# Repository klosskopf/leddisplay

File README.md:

# leddisplay
A 10x10 led display with ice40 FPGA

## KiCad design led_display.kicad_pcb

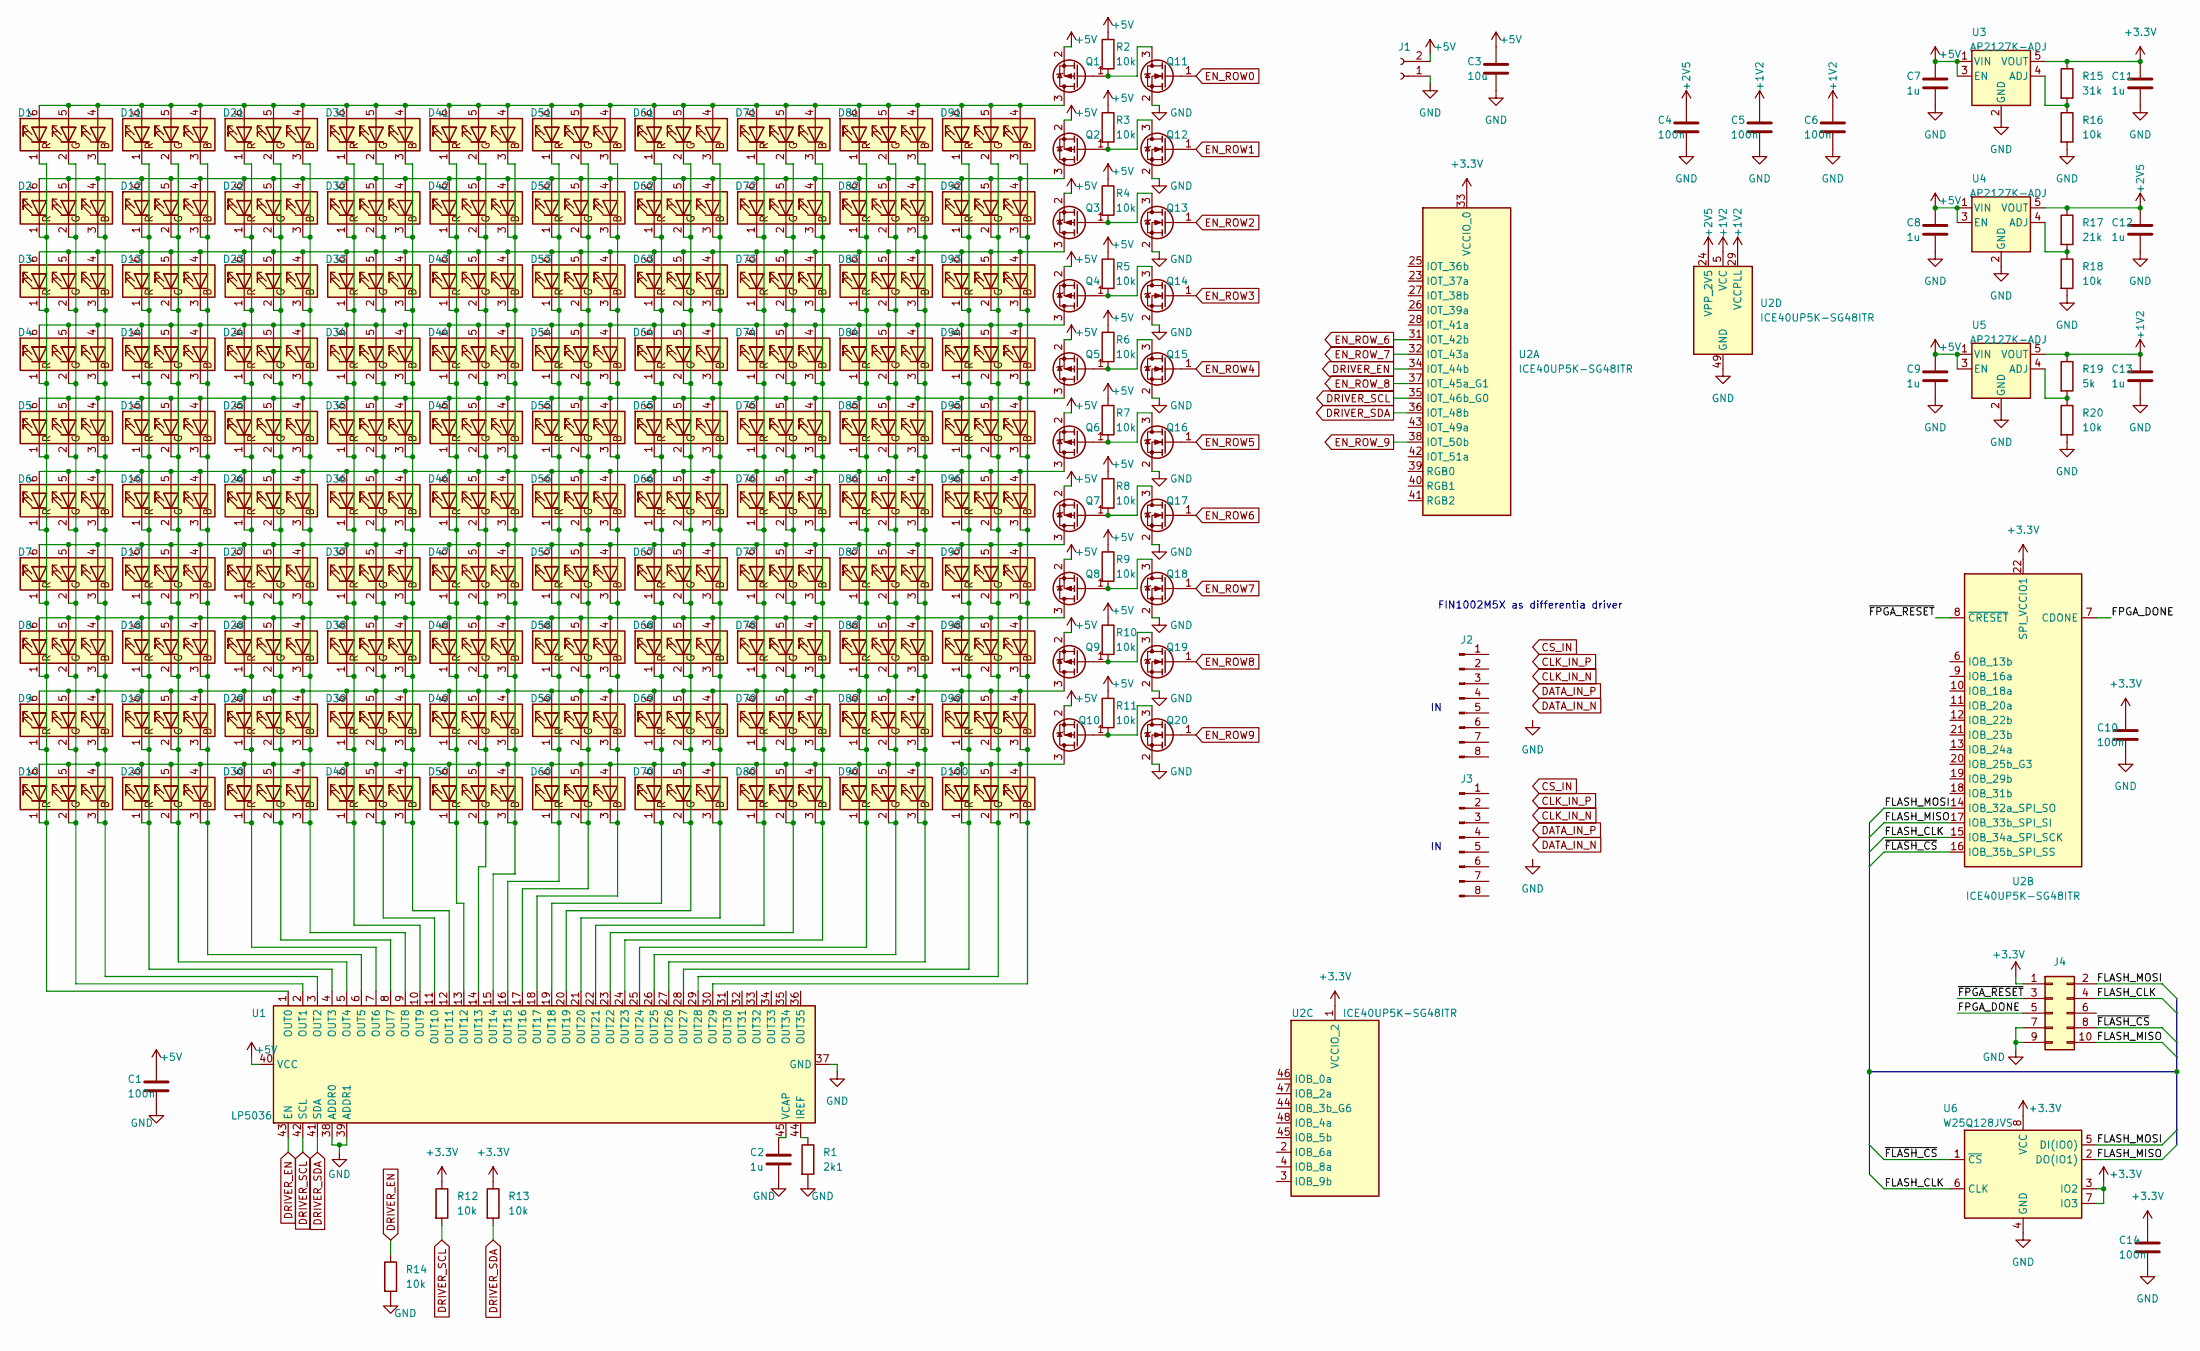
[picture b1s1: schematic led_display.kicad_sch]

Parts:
C1, C4, C5, C6, C10, C14: 100n; C_0603_1608Metric
C2, C7, C8, C9, C11, C12, C13: 1u; C_1206_3216Metric
C3: 10u; C_1206_3216Metric
D1, D2, D3, D4, D5, D6, D7, D8, D9, D10, D11, D12, D13, D14, D15, D16, D17, D18, D19, D20, D21, D22, D23, D24, D25, D26, D27, D28, D29, D30, D31, D32, D33, D34, D35, D36, D37, D38, D39, D40, D41, D42, D43, D44, D45, D46, D47, D48, D49, D50, D51, D52, D53, D54, D55, D56, D57, D58, D59, D60, D61, D62, D63, D64, D65, D66, D67, D68, D69, D70, D71, D72, D73, D74, D75, D76, D77, D78, D79, D80, D81, D82, D83, D84, D85, D86, D87, D88, D89, D90, D91, D92, D93, D94, D95, D96, D97, D98, D99, D100: LED_RGB; LED_RGB_5050-6
J1: Conn_01x02_Female; Molex_PicoBlade_53261-0271_1x02-1MP_P1.25mm_Horizontal
J2, J3: Conn_01x08_Male; Molex_PicoBlade_53261-0871_1x08-1MP_P1.25mm_Horizontal
J4: Conn_02x05_Odd_Even; PinHeader_2x05_P2.54mm_Vertical_SMD
Q1, Q2, Q3, Q4, Q5, Q6, Q7, Q8, Q9, Q10: Q_PMOS_GSD; SOT-23
Q11, Q12, Q13, Q14, Q15, Q16, Q17, Q18, Q19, Q20: Q_NMOS_GSD; SOT-23
R1: 2k1; R_0603_1608Metric
R2, R3, R4, R5, R6, R7, R8, R9, R10, R11, R12, R13, R14, R16, R18, R20: 10k; R_0603_1608Metric
R15: 31k; R_0603_1608Metric
R17: 21k; R_0603_1608Metric
R19: 5k; R_0603_1608Metric
U1: LP5036; VQFN-46-1EP_5x6mm_P0.4mm_EP2.8x3.8mm
U2: ICE40UP5K-SG48ITR; QFN-48-1EP_7x7mm_P0.5mm_EP5.6x5.6mm
U3, U4, U5: AP2127K-ADJ; SOT-23-5
U6: W25Q128JVS; SOIC-8_5.23x5.23mm_P1.27mm

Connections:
+1V2: C5.1, C6.1, C13.1, R19.1, U2.5 (VCC), U2.29 (VCCPLL), U2.30 (VCC), U5.5 (VOUT)
+2V5: C4.1, C12.1, R17.1, U2.24 (VPP_2V5), U4.5 (VOUT)
+3.3V: C10.1, C11.1, C14.1, J4.1, R12.1, R13.1, R15.1, U2.1 (VCCIO_2), U2.22 (SPI_VCCIO1), U2.33 (VCCIO_0), U3.5 (VOUT), U6.3 (IO2), U6.7 (IO3), U6.8 (VCC)
+5V: C1.1, C3.1, C7.1, C8.1, C9.1, J1.2, Q1.2 (S), Q2.2 (S), Q3.2 (S), Q4.2 (S), Q5.2 (S), Q6.2 (S), Q7.2 (S), Q8.2 (S), Q9.2 (S), Q10.2 (S), R2.1, R3.1, R4.1, R5.1, R6.1, R7.1, R8.1, R9.1, R10.1, R11.1, U1.40 (VCC), U3.1 (VIN), U3.3 (EN), U4.1 (VIN), U4.3 (EN), U5.1 (VIN), U5.3 (EN)
/FLASH_CLK: J4.4, U2.15 (IOB_34a_SPI_SCK), U6.6 (CLK)
/FLASH_MISO: J4.10, U2.17 (IOB_33b_SPI_SI), U6.2 (DO(IO1))
/FLASH_MOSI: J4.2, U2.14 (IOB_32a_SPI_SO), U6.5 (DI(IO0))
/FPGA_DONE: J4.5, U2.7 (CDONE)
/~FLASH_CS: J4.8, U2.16 (IOB_35b_SPI_SS), U6.1 (~CS)
/~FPGA_RESET: J4.3, U2.8 (~CRESET)
DRIVER_EN: R14.1, U1.43 (EN), U2.34 (IOT_44b)
DRIVER_SCL: R12.2, U1.42 (SCL), U2.35 (IOT_46b_G0)
DRIVER_SDA: R13.2, U1.41 (SDA), U2.36 (IOT_48b)
EN_ROW0: Q11.1 (G)
EN_ROW1: Q12.1 (G)
EN_ROW2: Q13.1 (G)
EN_ROW3: Q14.1 (G)
EN_ROW4: Q15.1 (G)
EN_ROW5: Q16.1 (G)
EN_ROW6: Q17.1 (G)
EN_ROW7: Q18.1 (G)
EN_ROW8: Q19.1 (G)
EN_ROW9: Q20.1 (G)
EN_ROW_6: U2.31 (IOT_42b)
EN_ROW_7: U2.32 (IOT_43a)
EN_ROW_8: U2.37 (IOT_45a_G1)
EN_ROW_9: U2.38 (IOT_50b)
GND: C1.2, C2.2, C3.2, C4.2, C5.2, C6.2, C7.2, C8.2, C9.2, C10.2, C11.2, C12.2, C13.2, C14.2, J1.1, J4.7, J4.9, Q11.2 (S), Q12.2 (S), Q13.2 (S), Q14.2 (S), Q15.2 (S), Q16.2 (S), Q17.2 (S), Q18.2 (S), Q19.2 (S), Q20.2 (S), R1.2, R14.2, R16.2, R18.2, R20.2, U1.37 (GND), U1.38 (ADDR0), U1.39 (ADDR1), U1.46 (GND), U1.47 (GND), U2.49 (GND), U3.2 (GND), U4.2 (GND), U5.2 (GND), U6.4 (GND)
unnamed: D1.4 (BA), D1.5 (GA), D1.6 (RA), D11.4 (BA), D11.5 (GA), D11.6 (RA), D21.4 (BA), D21.5 (GA), D21.6 (RA), D31.4 (BA), D31.5 (GA), D31.6 (RA), D41.4 (BA), D41.5 (GA), D41.6 (RA), D51.4 (BA), D51.5 (GA), D51.6 (RA), D61.4 (BA), D61.5 (GA), D61.6 (RA), D71.4 (BA), D71.5 (GA), D71.6 (RA), D81.4 (BA), D81.5 (GA), D81.6 (RA), D91.4 (BA), D91.5 (GA), D91.6 (RA), Q1.3 (D)
unnamed: D1.3 (BK), D2.3 (BK), D3.3 (BK), D4.3 (BK), D5.3 (BK), D6.3 (BK), D7.3 (BK), D8.3 (BK), D9.3 (BK), D10.3 (BK), U1.3 (OUT2)
unnamed: D1.2 (GK), D2.2 (GK), D3.2 (GK), D4.2 (GK), D5.2 (GK), D6.2 (GK), D7.2 (GK), D8.2 (GK), D9.2 (GK), D10.2 (GK), U1.2 (OUT1)
unnamed: D1.1 (RK), D2.1 (RK), D3.1 (RK), D4.1 (RK), D5.1 (RK), D6.1 (RK), D7.1 (RK), D8.1 (RK), D9.1 (RK), D10.1 (RK), U1.1 (OUT0)
unnamed: D10.4 (BA), D10.5 (GA), D10.6 (RA), D20.4 (BA), D20.5 (GA), D20.6 (RA), D30.4 (BA), D30.5 (GA), D30.6 (RA), D40.4 (BA), D40.5 (GA), D40.6 (RA), D50.4 (BA), D50.5 (GA), D50.6 (RA), D60.4 (BA), D60.5 (GA), D60.6 (RA), D70.4 (BA), D70.5 (GA), D70.6 (RA), D80.4 (BA), D80.5 (GA), D80.6 (RA), D90.4 (BA), D90.5 (GA), D90.6 (RA), D100.4 (BA), D100.5 (GA), D100.6 (RA), Q10.3 (D)
unnamed: D11.3 (BK), D12.3 (BK), D13.3 (BK), D14.3 (BK), D15.3 (BK), D16.3 (BK), D17.3 (BK), D18.3 (BK), D19.3 (BK), D20.3 (BK), U1.6 (OUT5)
unnamed: D11.2 (GK), D12.2 (GK), D13.2 (GK), D14.2 (GK), D15.2 (GK), D16.2 (GK), D17.2 (GK), D18.2 (GK), D19.2 (GK), D20.2 (GK), U1.5 (OUT4)
unnamed: D11.1 (RK), D12.1 (RK), D13.1 (RK), D14.1 (RK), D15.1 (RK), D16.1 (RK), D17.1 (RK), D18.1 (RK), D19.1 (RK), D20.1 (RK), U1.4 (OUT3)
unnamed: D2.4 (BA), D2.5 (GA), D2.6 (RA), D12.4 (BA), D12.5 (GA), D12.6 (RA), D22.4 (BA), D22.5 (GA), D22.6 (RA), D32.4 (BA), D32.5 (GA), D32.6 (RA), D42.4 (BA), D42.5 (GA), D42.6 (RA), D52.4 (BA), D52.5 (GA), D52.6 (RA), D62.4 (BA), D62.5 (GA), D62.6 (RA), D72.4 (BA), D72.5 (GA), D72.6 (RA), D82.4 (BA), D82.5 (GA), D82.6 (RA), D92.4 (BA), D92.5 (GA), D92.6 (RA), Q2.3 (D)
unnamed: D3.4 (BA), D3.5 (GA), D3.6 (RA), D13.4 (BA), D13.5 (GA), D13.6 (RA), D23.4 (BA), D23.5 (GA), D23.6 (RA), D33.4 (BA), D33.5 (GA), D33.6 (RA), D43.4 (BA), D43.5 (GA), D43.6 (RA), D53.4 (BA), D53.5 (GA), D53.6 (RA), D63.4 (BA), D63.5 (GA), D63.6 (RA), D73.4 (BA), D73.5 (GA), D73.6 (RA), D83.4 (BA), D83.5 (GA), D83.6 (RA), D93.4 (BA), D93.5 (GA), D93.6 (RA), Q3.3 (D)
unnamed: D4.4 (BA), D4.5 (GA), D4.6 (RA), D14.4 (BA), D14.5 (GA), D14.6 (RA), D24.4 (BA), D24.5 (GA), D24.6 (RA), D34.4 (BA), D34.5 (GA), D34.6 (RA), D44.4 (BA), D44.5 (GA), D44.6 (RA), D54.4 (BA), D54.5 (GA), D54.6 (RA), D64.4 (BA), D64.5 (GA), D64.6 (RA), D74.4 (BA), D74.5 (GA), D74.6 (RA), D84.4 (BA), D84.5 (GA), D84.6 (RA), D94.4 (BA), D94.5 (GA), D94.6 (RA), Q4.3 (D)
unnamed: D5.4 (BA), D5.5 (GA), D5.6 (RA), D15.4 (BA), D15.5 (GA), D15.6 (RA), D25.4 (BA), D25.5 (GA), D25.6 (RA), D35.4 (BA), D35.5 (GA), D35.6 (RA), D45.4 (BA), D45.5 (GA), D45.6 (RA), D55.4 (BA), D55.5 (GA), D55.6 (RA), D65.4 (BA), D65.5 (GA), D65.6 (RA), D75.4 (BA), D75.5 (GA), D75.6 (RA), D85.4 (BA), D85.5 (GA), D85.6 (RA), D95.4 (BA), D95.5 (GA), D95.6 (RA), Q5.3 (D)
unnamed: D6.4 (BA), D6.5 (GA), D6.6 (RA), D16.4 (BA), D16.5 (GA), D16.6 (RA), D26.4 (BA), D26.5 (GA), D26.6 (RA), D36.4 (BA), D36.5 (GA), D36.6 (RA), D46.4 (BA), D46.5 (GA), D46.6 (RA), D56.4 (BA), D56.5 (GA), D56.6 (RA), D66.4 (BA), D66.5 (GA), D66.6 (RA), D76.4 (BA), D76.5 (GA), D76.6 (RA), D86.4 (BA), D86.5 (GA), D86.6 (RA), D96.4 (BA), D96.5 (GA), D96.6 (RA), Q6.3 (D)
unnamed: D7.4 (BA), D7.5 (GA), D7.6 (RA), D17.4 (BA), D17.5 (GA), D17.6 (RA), D27.4 (BA), D27.5 (GA), D27.6 (RA), D37.4 (BA), D37.5 (GA), D37.6 (RA), D47.4 (BA), D47.5 (GA), D47.6 (RA), D57.4 (BA), D57.5 (GA), D57.6 (RA), D67.4 (BA), D67.5 (GA), D67.6 (RA), D77.4 (BA), D77.5 (GA), D77.6 (RA), D87.4 (BA), D87.5 (GA), D87.6 (RA), D97.4 (BA), D97.5 (GA), D97.6 (RA), Q7.3 (D)
unnamed: D8.4 (BA), D8.5 (GA), D8.6 (RA), D18.4 (BA), D18.5 (GA), D18.6 (RA), D28.4 (BA), D28.5 (GA), D28.6 (RA), D38.4 (BA), D38.5 (GA), D38.6 (RA), D48.4 (BA), D48.5 (GA), D48.6 (RA), D58.4 (BA), D58.5 (GA), D58.6 (RA), D68.4 (BA), D68.5 (GA), D68.6 (RA), D78.4 (BA), D78.5 (GA), D78.6 (RA), D88.4 (BA), D88.5 (GA), D88.6 (RA), D98.4 (BA), D98.5 (GA), D98.6 (RA), Q8.3 (D)
unnamed: D9.4 (BA), D9.5 (GA), D9.6 (RA), D19.4 (BA), D19.5 (GA), D19.6 (RA), D29.4 (BA), D29.5 (GA), D29.6 (RA), D39.4 (BA), D39.5 (GA), D39.6 (RA), D49.4 (BA), D49.5 (GA), D49.6 (RA), D59.4 (BA), D59.5 (GA), D59.6 (RA), D69.4 (BA), D69.5 (GA), D69.6 (RA), D79.4 (BA), D79.5 (GA), D79.6 (RA), D89.4 (BA), D89.5 (GA), D89.6 (RA), D99.4 (BA), D99.5 (GA), D99.6 (RA), Q9.3 (D)
unnamed: D21.3 (BK), D22.3 (BK), D23.3 (BK), D24.3 (BK), D25.3 (BK), D26.3 (BK), D27.3 (BK), D28.3 (BK), D29.3 (BK), D30.3 (BK), U1.9 (OUT8)
unnamed: D21.2 (GK), D22.2 (GK), D23.2 (GK), D24.2 (GK), D25.2 (GK), D26.2 (GK), D27.2 (GK), D28.2 (GK), D29.2 (GK), D30.2 (GK), U1.8 (OUT7)
unnamed: D21.1 (RK), D22.1 (RK), D23.1 (RK), D24.1 (RK), D25.1 (RK), D26.1 (RK), D27.1 (RK), D28.1 (RK), D29.1 (RK), D30.1 (RK), U1.7 (OUT6)
unnamed: D31.3 (BK), D32.3 (BK), D33.3 (BK), D34.3 (BK), D35.3 (BK), D36.3 (BK), D37.3 (BK), D38.3 (BK), D39.3 (BK), D40.3 (BK), U1.12 (OUT11)
unnamed: D31.2 (GK), D32.2 (GK), D33.2 (GK), D34.2 (GK), D35.2 (GK), D36.2 (GK), D37.2 (GK), D38.2 (GK), D39.2 (GK), D40.2 (GK), U1.11 (OUT10)
unnamed: D31.1 (RK), D32.1 (RK), D33.1 (RK), D34.1 (RK), D35.1 (RK), D36.1 (RK), D37.1 (RK), D38.1 (RK), D39.1 (RK), D40.1 (RK), U1.10 (OUT9)
unnamed: D41.3 (BK), D42.3 (BK), D43.3 (BK), D44.3 (BK), D45.3 (BK), D46.3 (BK), D47.3 (BK), D48.3 (BK), D49.3 (BK), D50.3 (BK), U1.15 (OUT14)
unnamed: D41.2 (GK), D42.2 (GK), D43.2 (GK), D44.2 (GK), D45.2 (GK), D46.2 (GK), D47.2 (GK), D48.2 (GK), D49.2 (GK), D50.2 (GK), U1.14 (OUT13)
unnamed: D41.1 (RK), D42.1 (RK), D43.1 (RK), D44.1 (RK), D45.1 (RK), D46.1 (RK), D47.1 (RK), D48.1 (RK), D49.1 (RK), D50.1 (RK), U1.13 (OUT12)
unnamed: D51.3 (BK), D52.3 (BK), D53.3 (BK), D54.3 (BK), D55.3 (BK), D56.3 (BK), D57.3 (BK), D58.3 (BK), D59.3 (BK), D60.3 (BK), U1.18 (OUT17)
unnamed: D51.2 (GK), D52.2 (GK), D53.2 (GK), D54.2 (GK), D55.2 (GK), D56.2 (GK), D57.2 (GK), D58.2 (GK), D59.2 (GK), D60.2 (GK), U1.17 (OUT16)
unnamed: D51.1 (RK), D52.1 (RK), D53.1 (RK), D54.1 (RK), D55.1 (RK), D56.1 (RK), D57.1 (RK), D58.1 (RK), D59.1 (RK), D60.1 (RK), U1.16 (OUT15)
unnamed: D61.3 (BK), D62.3 (BK), D63.3 (BK), D64.3 (BK), D65.3 (BK), D66.3 (BK), D67.3 (BK), D68.3 (BK), D69.3 (BK), D70.3 (BK), U1.21 (OUT20)
unnamed: D61.2 (GK), D62.2 (GK), D63.2 (GK), D64.2 (GK), D65.2 (GK), D66.2 (GK), D67.2 (GK), D68.2 (GK), D69.2 (GK), D70.2 (GK), U1.20 (OUT19)
unnamed: D61.1 (RK), D62.1 (RK), D63.1 (RK), D64.1 (RK), D65.1 (RK), D66.1 (RK), D67.1 (RK), D68.1 (RK), D69.1 (RK), D70.1 (RK), U1.19 (OUT18)
unnamed: D71.3 (BK), D72.3 (BK), D73.3 (BK), D74.3 (BK), D75.3 (BK), D76.3 (BK), D77.3 (BK), D78.3 (BK), D79.3 (BK), D80.3 (BK), U1.24 (OUT23)
unnamed: D71.2 (GK), D72.2 (GK), D73.2 (GK), D74.2 (GK), D75.2 (GK), D76.2 (GK), D77.2 (GK), D78.2 (GK), D79.2 (GK), D80.2 (GK), U1.23 (OUT22)
unnamed: D71.1 (RK), D72.1 (RK), D73.1 (RK), D74.1 (RK), D75.1 (RK), D76.1 (RK), D77.1 (RK), D78.1 (RK), D79.1 (RK), D80.1 (RK), U1.22 (OUT21)
unnamed: D81.3 (BK), D82.3 (BK), D83.3 (BK), D84.3 (BK), D85.3 (BK), D86.3 (BK), D87.3 (BK), D88.3 (BK), D89.3 (BK), D90.3 (BK), U1.27 (OUT26)
unnamed: D81.2 (GK), D82.2 (GK), D83.2 (GK), D84.2 (GK), D85.2 (GK), D86.2 (GK), D87.2 (GK), D88.2 (GK), D89.2 (GK), D90.2 (GK), U1.26 (OUT25)
unnamed: D81.1 (RK), D82.1 (RK), D83.1 (RK), D84.1 (RK), D85.1 (RK), D86.1 (RK), D87.1 (RK), D88.1 (RK), D89.1 (RK), D90.1 (RK), U1.25 (OUT24)
unnamed: D91.3 (BK), D92.3 (BK), D93.3 (BK), D94.3 (BK), D95.3 (BK), D96.3 (BK), D97.3 (BK), D98.3 (BK), D99.3 (BK), D100.3 (BK), U1.30 (OUT29)
unnamed: D91.2 (GK), D92.2 (GK), D93.2 (GK), D94.2 (GK), D95.2 (GK), D96.2 (GK), D97.2 (GK), D98.2 (GK), D99.2 (GK), D100.2 (GK), U1.29 (OUT28)
unnamed: D91.1 (RK), D92.1 (RK), D93.1 (RK), D94.1 (RK), D95.1 (RK), D96.1 (RK), D97.1 (RK), D98.1 (RK), D99.1 (RK), D100.1 (RK), U1.28 (OUT27)
unnamed: Q1.1 (G), Q11.3 (D), R2.2
unnamed: Q10.1 (G), Q20.3 (D), R11.2
unnamed: Q2.1 (G), Q12.3 (D), R3.2
unnamed: Q3.1 (G), Q13.3 (D), R4.2
unnamed: Q4.1 (G), Q14.3 (D), R5.2
unnamed: Q5.1 (G), Q15.3 (D), R6.2
unnamed: Q6.1 (G), Q16.3 (D), R7.2
unnamed: Q7.1 (G), Q17.3 (D), R8.2
unnamed: Q8.1 (G), Q18.3 (D), R9.2
unnamed: Q9.1 (G), Q19.3 (D), R10.2
unnamed: R1.1, U1.44 (IREF)
unnamed: C2.1, U1.45 (VCAP)
unnamed: R15.2, R16.1, U3.4 (ADJ)
unnamed: R17.2, R18.1, U4.4 (ADJ)
unnamed: R19.2, R20.1, U5.4 (ADJ)

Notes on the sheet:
FIN1002M5X as differentia driver

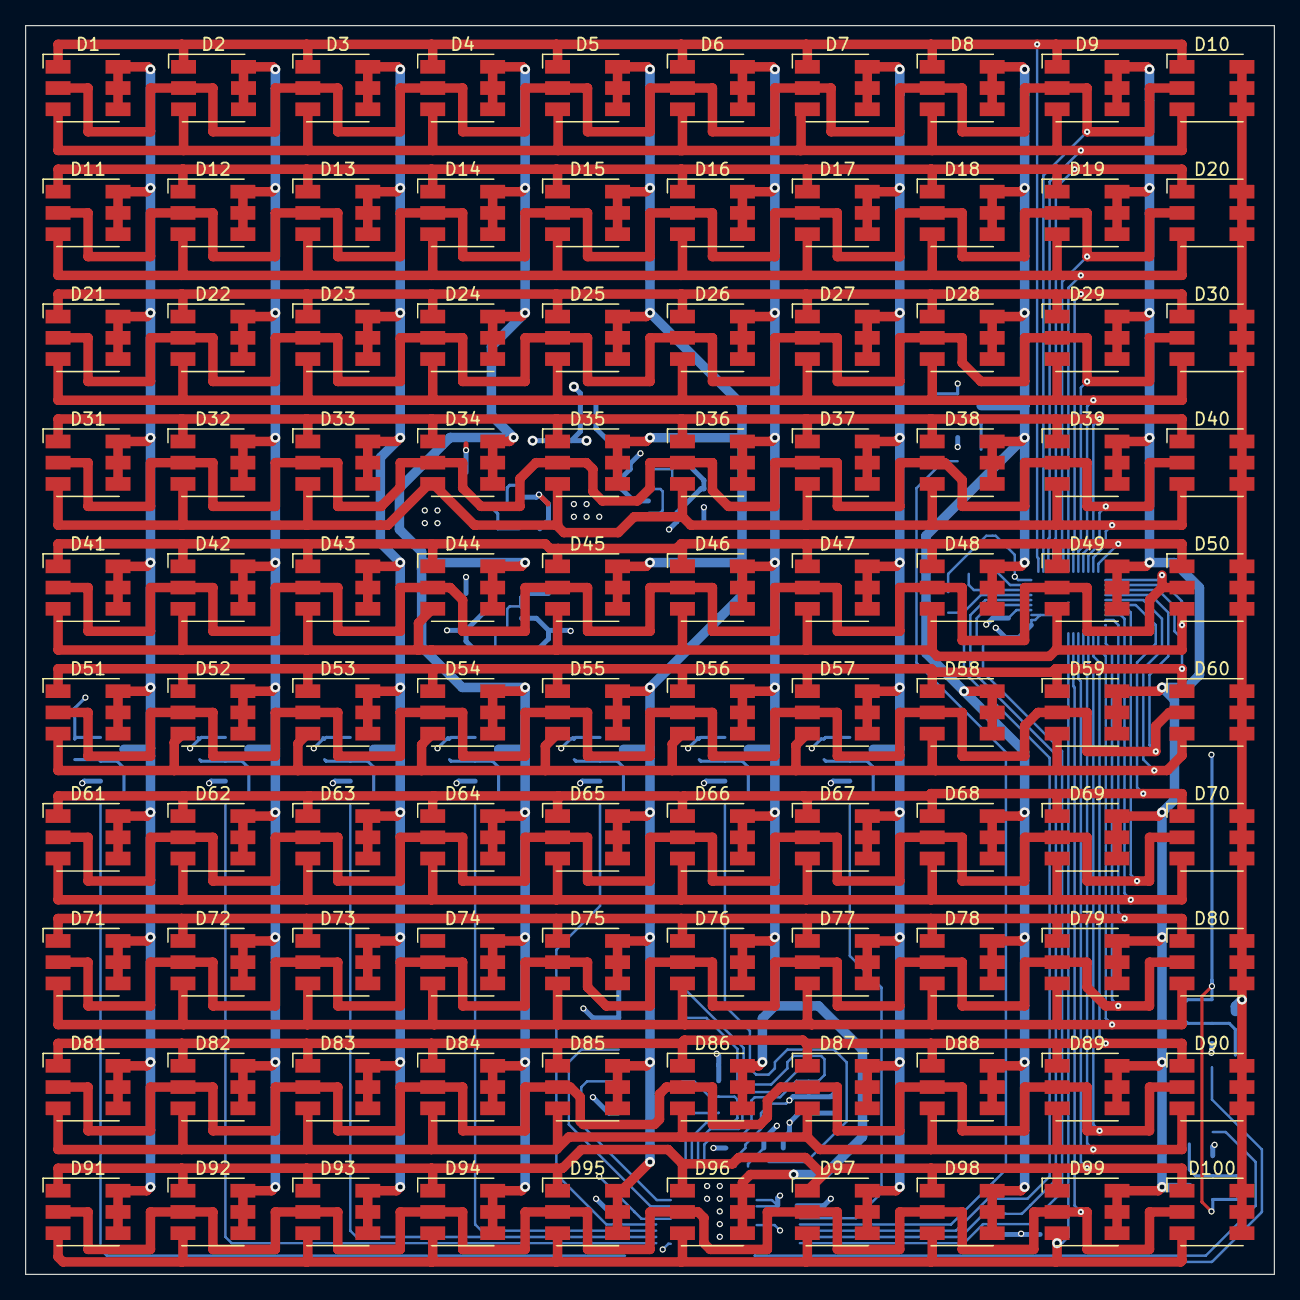
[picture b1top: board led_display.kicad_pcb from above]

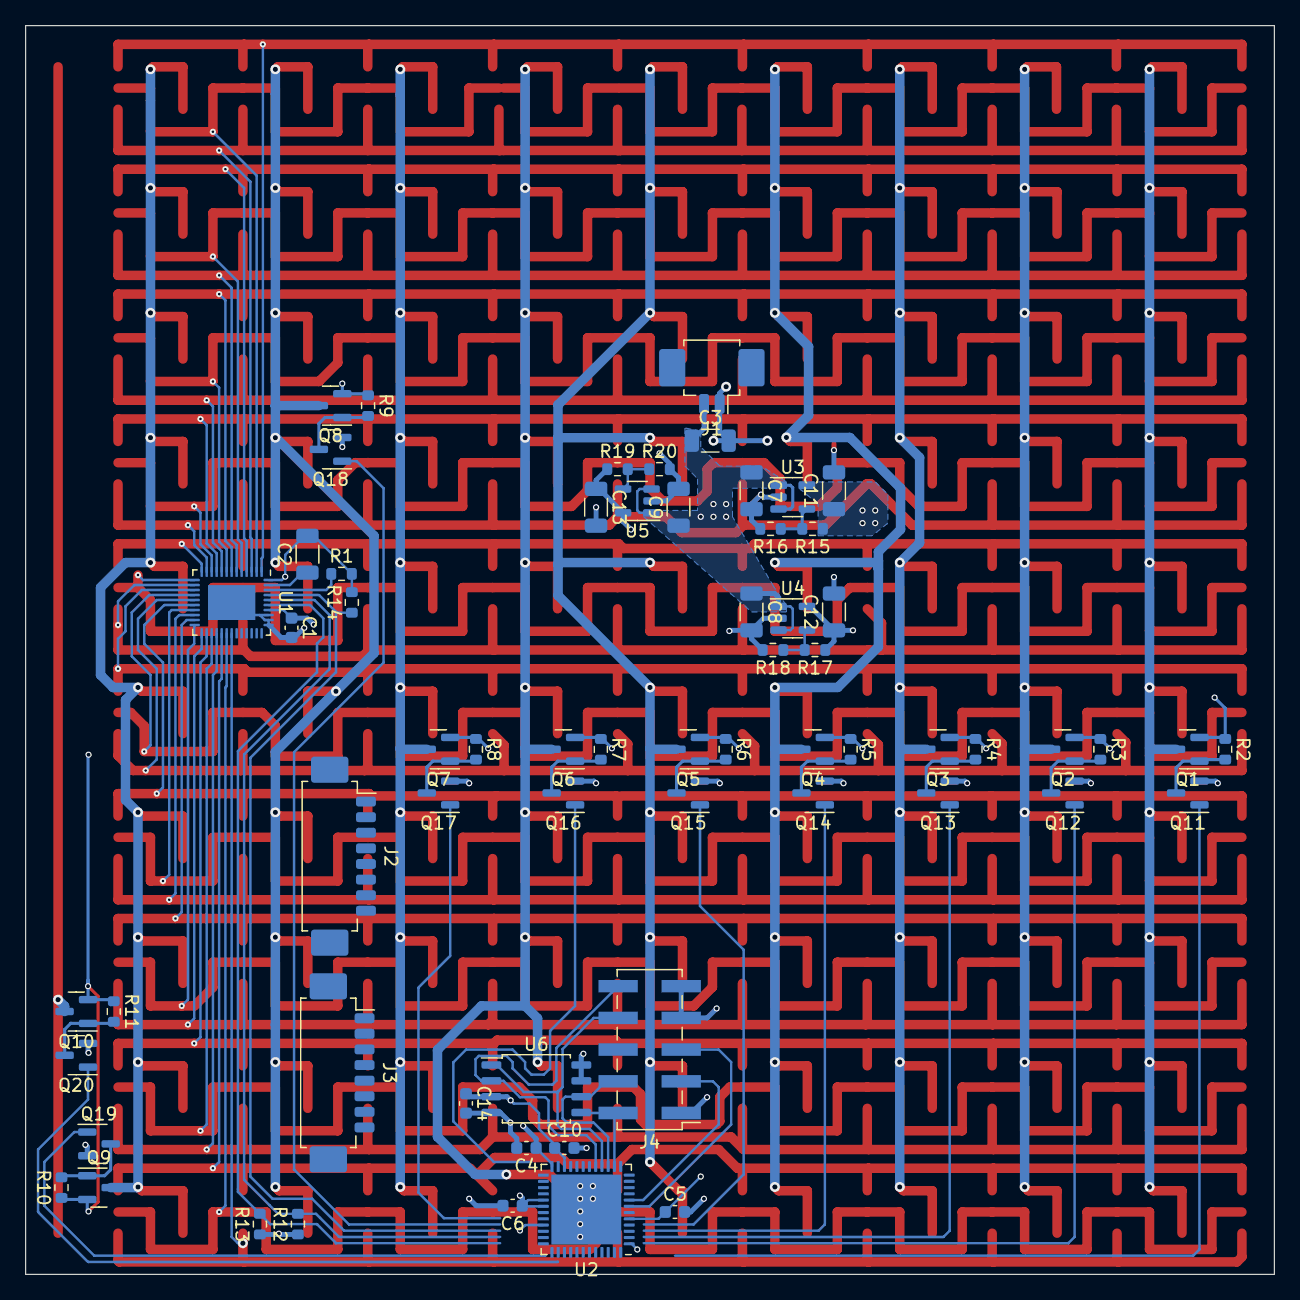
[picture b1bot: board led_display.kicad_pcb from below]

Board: 4 copper layers, 100.0 x 100.0 mm, 164 parts (64 on the bottom side), 69 nets.

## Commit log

2024-03-21 added FPGA
2024-03-22 started placement of LDOs
2024-03-24 finished placement; resumed layout
2024-03-24 routet LDOs
2024-03-27 layout of supply
